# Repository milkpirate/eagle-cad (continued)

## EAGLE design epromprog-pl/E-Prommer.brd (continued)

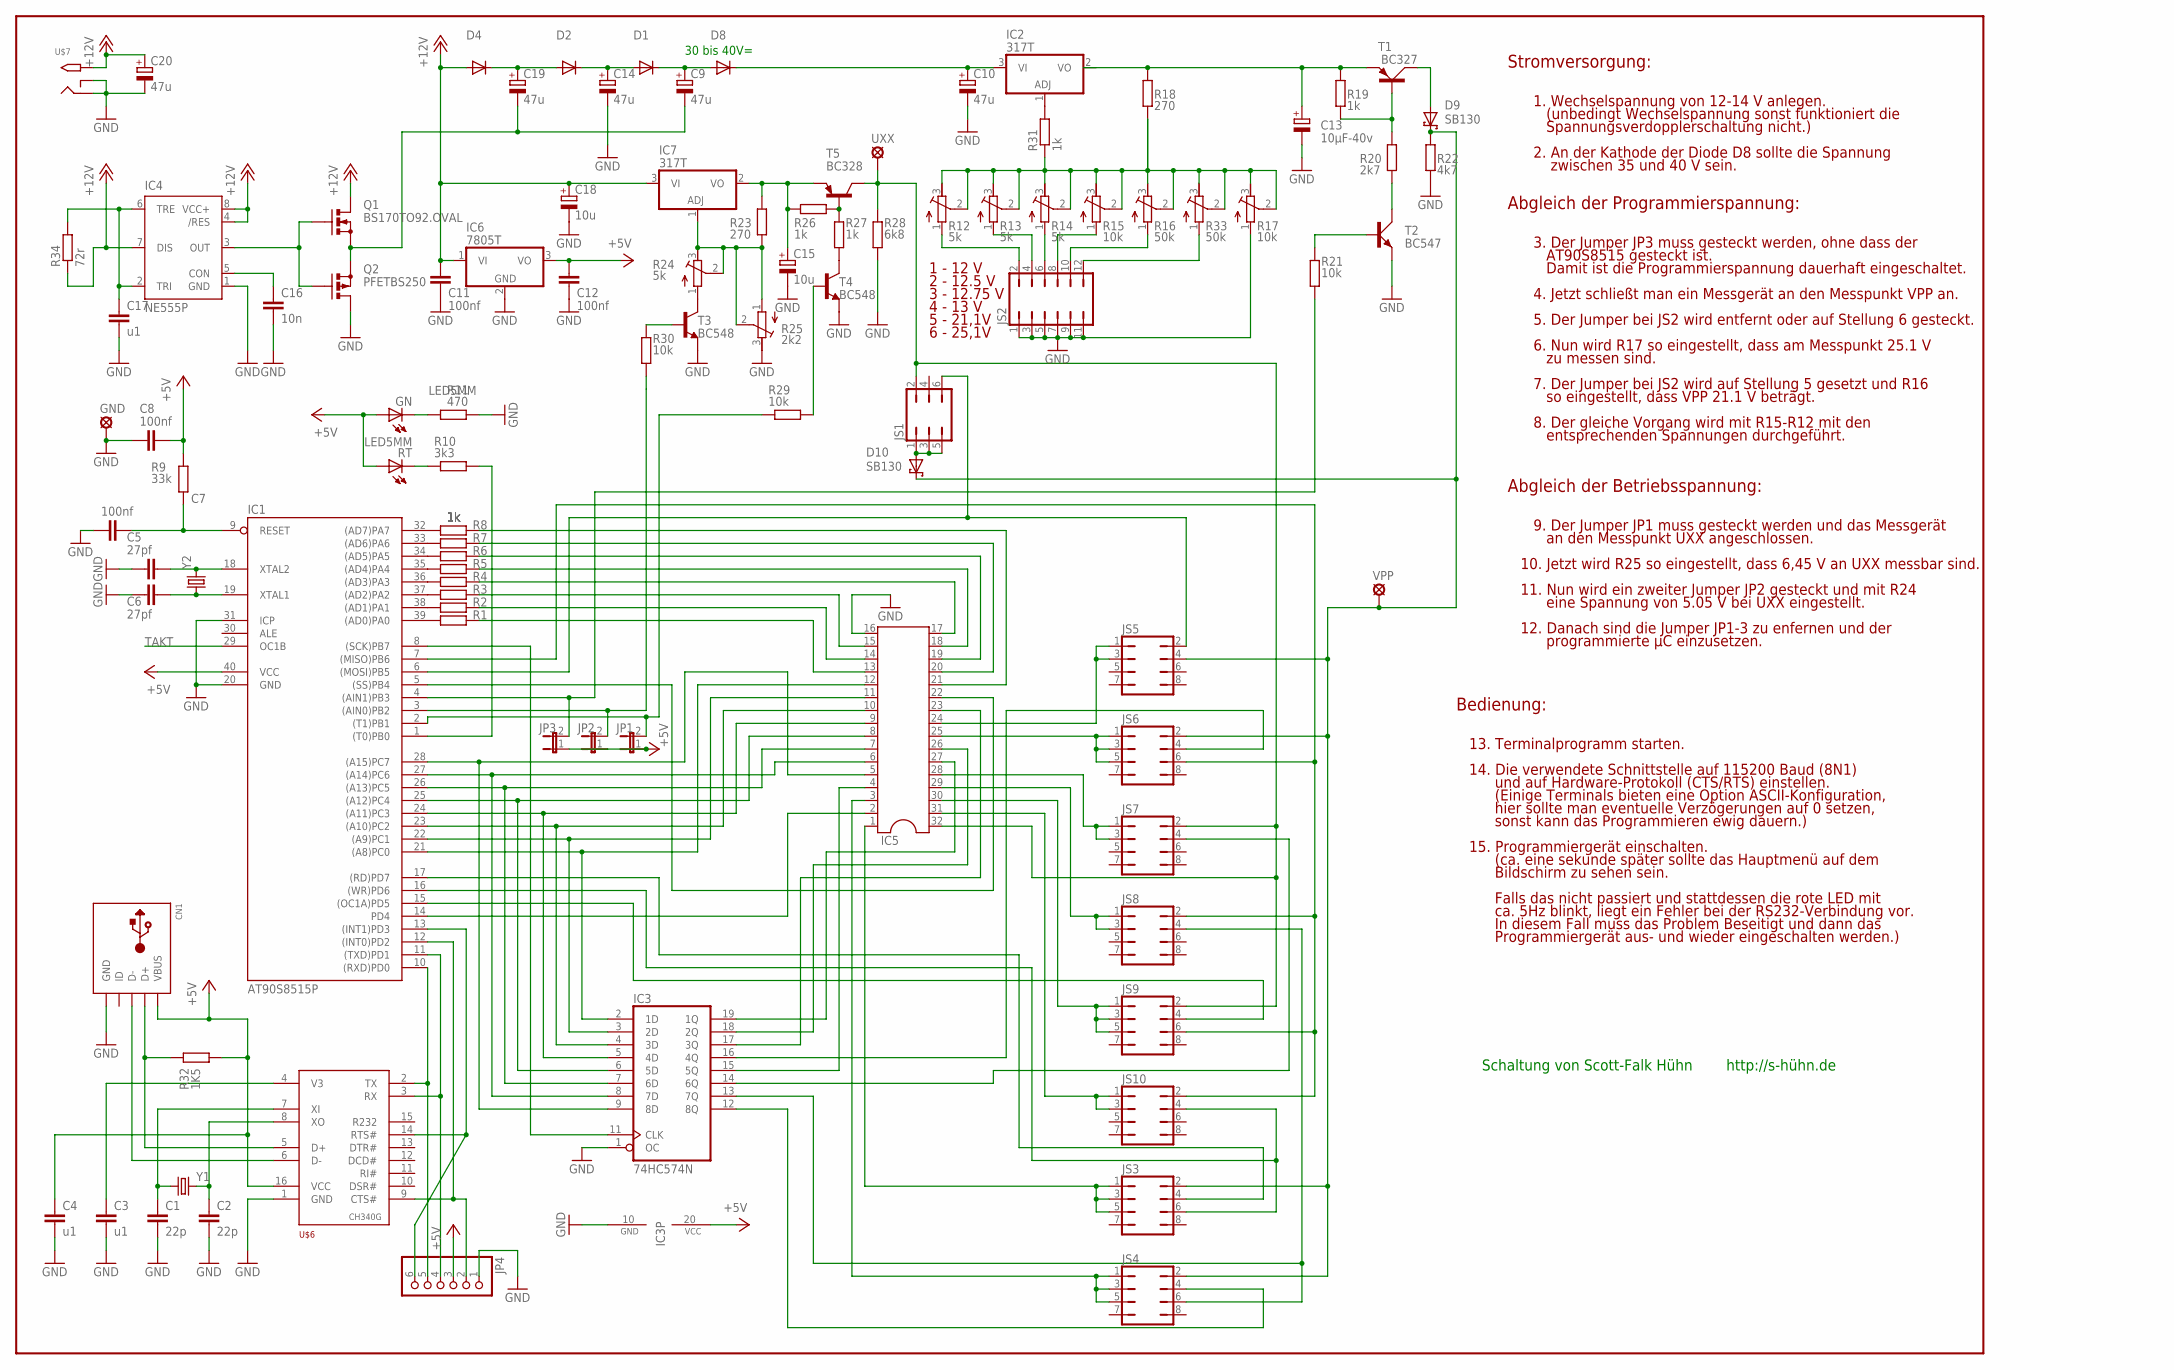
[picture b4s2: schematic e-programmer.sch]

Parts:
C1, C2: 22p; C025-025X050
C3, C4, C17: u1; C025-025X050
C5, C6: 27pf; C025-024X044
C7, C8, C11, C12: 100nf; C025-024X044
C9, C10, C14, C19, C20: 47u; E2,5-7
C13: 10µF-40v; E2,5-5
C15, C18: 10u; E2,5-7
C16: 10n; C025-025X050
CN1: USBTHM; USB-MINIB-THM
D1, D2, D4, D8: 1N4004; DO35-10
D9, D10: SB130; DO35-7
GN: LED5MM
GND: LSP10
IC1: AT90S8515P; DIL40
IC2, IC7: 317T; TO220H
IC3: 74HC574N; DIL20
IC4: NE555P; DIL-08
IC5: DIL32
IC6: 7805T; TO220H
JP1, JP2, JP3: JP1E; JP1
JP4: PINHD-1X6; 1X06
JS1: JP3Q
JS2: JP6Q
JS3, JS4, JS5, JS6, JS7, JS8, JS9, JS10: JP4Q
Q1: BS170TO92.OVAL; TO92-OVAL
Q2: PFETBS250; TO92-OVAL
R1, R2, R3, R4, R5, R6, R7, R8, R19, R26, R27, R31: 1k; 0207/7
R9: 33k; 0204/7
R10: 3k3; 0204/7
R11: 470; 0204/7
R12, R13, R14, R24: 5k; RTRIM3296W
R15, R17: 10k; RTRIM3296W
R16, R33: 50k; RTRIM3296W
R18, R23: 270; 0207/7
R20: 2k7; 0207/7
R21, R29, R30: 10k; 0207/7
R22: 4k7; 0207/7
R25: 2k2; RTRIM3296W
R28: 6k8; 0207/7
R32: 1K5; 0204/7
R34: 72r; 0204/7
RT: LED5MM
T1: BC327; SOT54A
T2: BC547; SOT54A
T3, T4: BC548; TO92
T5: BC328; TO92
U$6: CH340G; SO16
U$7: 2.1MMJACKTHM; PJ-102A
UXX: LSP10
VPP: LSP10
Y1, Y2: CRYSTALHC49US; HC49US

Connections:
!CE: IC1.5 ((SS)PB4), IC5.22
!OE: IC1.6 ((MOSI)PB5), JS1.6, JS5.2
!PR: IC1.7 ((MISO)PB6), JS6.6, JS8.2, JS9.6, JS10.2
+5V: C4.1, C8.2, C12.1, CN1.VBUS, GN.A, IC1.40 (VCC), IC3.20 (VCC), IC6.3 (VO), JP1.1, JP2.1, JP3.1, JP4.3, R9.2, R32.1, RT.A, U$6.16 (VCC)
A0: IC1.21 ((A8)PC0), IC3.2 (1D), IC5.12
A1: IC1.22 ((A9)PC1), IC3.3 (2D), IC5.11
A2: IC1.23 ((A10)PC2), IC3.4 (3D), IC5.10
A3: IC1.24 ((A11)PC3), IC3.5 (4D), IC5.9
A4: IC1.25 ((A12)PC4), IC3.6 (5D), IC5.8
A5: IC1.26 ((A13)PC5), IC3.7 (6D), IC5.7
A6: IC1.27 ((A14)PC6), IC3.8 (7D), IC5.6
A7: IC1.28 ((A15)PC7), IC3.9 (8D), IC5.5
A8: IC3.19 (1Q), IC5.27
A9: IC3.18 (2Q), IC5.26
A10: IC3.17 (3Q), IC5.23
A11: IC3.16 (4Q), JS6.4
A12: IC3.15 (5Q), IC5.4
A13: IC3.14 (6Q), JS7.4
A14: IC3.13 (7Q), JS4.6, JS8.4
A15: IC3.12 (8Q), JS4.4
A16: IC1.14 (PD4), IC5.2
A17: IC1.15 ((OC1A)PD5), JS9.4
A18: IC1.16 ((WR)PD6), JS3.6, JS10.4
A19: IC1.17 ((RD)PD7), JS3.4
CTS: IC1.12 ((INT0)PD2), JP4.2, U$6.9 (CTS#)
D0: IC5.13, R1.2
D1: IC5.14, R2.2
D2: IC5.15, R3.2
D3: IC5.17, R4.2
D4: IC5.18, R5.2
D5: IC5.19, R6.2
D6: IC5.20, R7.2
D7: IC5.21, R8.2
GND: C1.2, C2.2, C3.2, C4.2, C5.1, C6.1, C7.1, C8.1, C10.-, C11.2, C12.2, C13.-, C14.-, C15.-, C16.2, C17.2, C18.-, C20.-, CN1.GND, GND.MP, IC1.20 (GND), IC1.31 (ICP), IC3.1 (OC), IC3.10 (GND), IC4.1 (GND), IC5.16, IC6.2 (GND), JP4.1, JS2.1, JS2.3, JS2.5, JS2.7, JS2.9, JS2.11, Q2.1 (D), R11.2, R17.1 (E), R22.1, R25.3 (A), R28.1, T2.E, T3.1 (E), T4.1 (E), U$6.1 (GND), U$7.RING, U$7.RING_SW; also elsewhere on the board
unnamed: IC1.32 ((AD7)PA7), R8.1
unnamed: IC1.33 ((AD6)PA6), R7.1
unnamed: IC1.34 ((AD5)PA5), R6.1
unnamed: IC1.35 ((AD4)PA4), R5.1
unnamed: IC1.36 ((AD3)PA3), R4.1
unnamed: IC1.37 ((AD2)PA2), R3.1
unnamed: IC1.38 ((AD1)PA1), R2.1
unnamed: IC1.39 ((AD0)PA0), R1.1
unnamed: IC1.8 ((SCK)PB7), IC3.11 (CLK)
unnamed: IC1.10 ((RXD)PD0), JP4.5, U$6.2 (TX)
unnamed: IC1.11 ((TXD)PD1), JP4.4, U$6.3 (RX)
unnamed: CN1.D+, R32.2, U$6.5 (D+)
unnamed: CN1.D-, U$6.6 (D-)
unnamed: C2.1, U$6.8 (XO), Y1.2
unnamed: C1.1, U$6.7 (XI), Y1.1
unnamed: C3.1, U$6.4 (V3)
unnamed: JS2.12, R33.1 (E)
unnamed: R10.1, RT.K (C)
unnamed: C16.1, IC4.5 (CON)
unnamed: C17.1, IC4.2 (TRI), IC4.6 (TRE), R34.2
unnamed: GN.K (C), R11.1
unnamed: IC5.3, JS4.1, JS4.3, JS4.5
unnamed: IC5.1, JS3.1, JS3.3, JS3.5
unnamed: IC5.24, JS5.1, JS5.3
unnamed: C7.2, IC1.9 (RESET), R9.1
unnamed: IC5.25, JS6.1, JS6.3, JS6.5
unnamed: JS2.2, R12.1 (E)
unnamed: JS2.4, R13.1 (E)
unnamed: IC5.28, JS7.1, JS7.3
unnamed: IC5.29, JS8.1, JS8.3
unnamed: IC1.1 ((T0)PB0), R10.2
unnamed: IC5.30, JS9.1, JS9.3, JS9.5
unnamed: JS2.6, R14.1 (E)
unnamed: IC5.31, JS10.1, JS10.3
unnamed: JS2.8, R15.1 (E)
unnamed: JS2.10, R16.1 (E)
unnamed: R12.2 (S), R12.3 (A), R13.2 (S), R13.3 (A), R14.2 (S), R14.3 (A), R15.2 (S), R15.3 (A), R16.2 (S), R16.3 (A), R17.2 (S), R17.3 (A), R18.1, R31.1, R33.2 (S), R33.3 (A)
unnamed: D10.A, JS1.1, JS1.3, JS1.5
unnamed: D9.A, T1.C
unnamed: R26.1, R27.2, T5.2 (B)
unnamed: R27.1, T4.3 (C)
unnamed: IC7.1 (ADJ), R23.1, R24.2 (S), R24.3 (A), R25.1 (E), R25.2 (S)
unnamed: R24.1 (E), T3.3 (C)
unnamed: C15.+, IC7.2 (VO), R23.2, R26.2, T5.1 (E)
unnamed: R29.2, T4.2 (B)
unnamed: C13.+, IC2.2 (VO), R18.2, R19.2, T1.E
unnamed: R30.2, T3.2 (B)
unnamed: R19.1, R20.2, T1.B
unnamed: R20.1, T2.C
unnamed: R21.2, T2.B
unnamed: IC2.1 (ADJ), R31.2
RTS: IC1.13 ((INT1)PD3), JP4.6, U$6.14 (RTS#)
TAKT: IC1.29 (OC1B)
UXX: IC5.32, JS1.2, JS7.2, JS9.2, R28.2, T5.3 (C), UXX.MP
VCC_5/6: IC1.3 ((AIN0)PB2), JP2.2, R30.1
VCC_EIN: IC1.2 ((T1)PB1), JP1.2, R29.1
VPP: D9.C, D10.C, JS3.2, JS4.2, JS5.4, JS6.2, R22.2, VPP.MP
VPP_EIN: IC1.4 ((AIN1)PB3), JP3.2, R21.1

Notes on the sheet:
Schaltung von Scott-Falk Hühn
http://s-hühn.de
1. Wechselspannung von 12-14 V anlegen.
(unbedingt Wechselspannung sonst funktioniert die
Spannungsverdopplerschaltung nicht.)
2. An der Kathode der Diode D8 sollte die Spannung
zwischen 35 und 40 V sein.
3. Der Jumper JP3 muss gesteckt werden, ohne dass der
4. Jetzt schließt man ein Messgerät an den Messpunkt VPP an.
5. Der Jumper bei JS2 wird entfernt oder auf Stellung 6 gesteckt.
6. Nun wird R17 so eingestellt, dass am Messpunkt 25.1 V
zu messen sind.
7. Der Jumper bei JS2 wird auf Stellung 5 gesetzt und R16
so eingestellt, dass VPP 21.1 V beträgt.
8. Der gleiche Vorgang wird mit R15-R12 mit den
entsprechenden Spannungen durchgeführt.
9. Der Jumper JP1 muss gesteckt werden und das Messgerät
an den Messpunkt UXX angeschlossen.
10. Jetzt wird R25 so eingestellt, dass 6,45 V an UXX messbar sind.
11. Nun wird ein zweiter Jumper JP2 gesteckt und mit R24
eine Spannung von 5.05 V bei UXX eingestellt.
Abgleich der Programmierspannung:
Abgleich der Betriebsspannung:
Bedienung:
13. Terminalprogramm starten.
14. Die verwendete Schnittstelle auf 115200 Baud (8N1)
und auf Hardware-Protokoll (CTS/RTS) einstellen.
(Einige Terminals bieten eine Option ASCII-Konfiguration,
hier sollte man eventuelle Verzögerungen auf 0 setzen,
sonst kann das Programmieren ewig dauern.)
15. Programmiergerät einschalten.
(ca. eine sekunde später sollte das Hauptmenü auf dem
Bildschirm zu sehen sein.
Falls das nicht passiert und stattdessen die rote LED mit
ca. 5Hz blinkt, liegt ein Fehler bei der RS232-Verbindung vor.
In diesem Fall muss das Problem Beseitigt und dann das
Programmiergerät aus- und wieder eingeschalten werden.)
Stromversorgung:
1 - 12 V
2 - 12.5 V

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
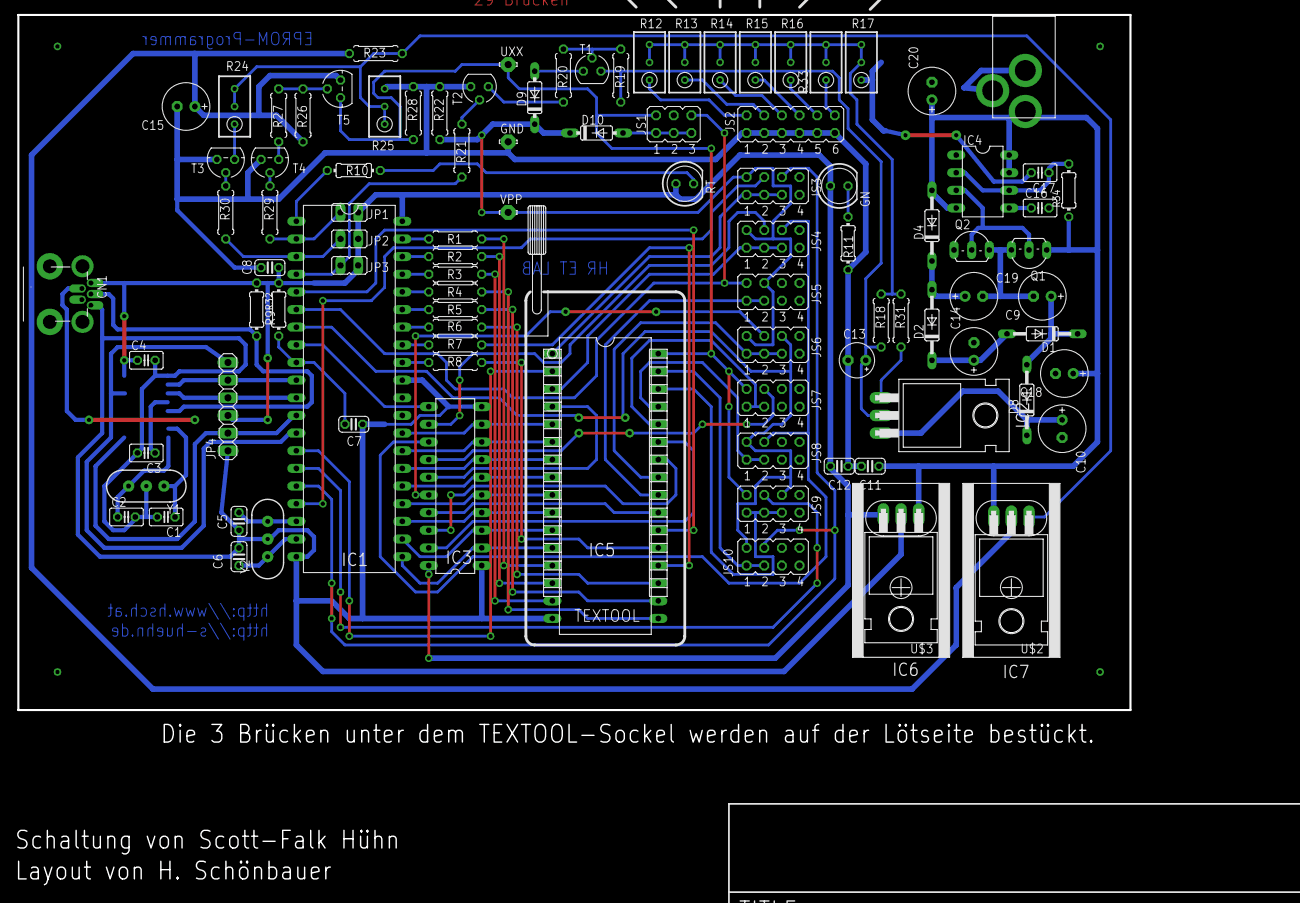
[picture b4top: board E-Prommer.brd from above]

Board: 2 copper layers, 160.0 x 100.0 mm, 103 parts (1 on the bottom side), 100 nets.

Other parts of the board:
U$1: SOCKEL
U$2, U$3: SK12/25
U$4: LETTER_P
U$5: DOCFIELD

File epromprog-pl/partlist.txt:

Partlist

Exported from E-Prommer.sch at 23.09.2014 12:23:19

EAGLE Version 6.1.0 Copyright (c) 1988-2012 CadSoft

Assembly variant: 

Part     Value          Device               Package       Library                 Sheet

C1       22p            C-EU025-025X050      C025-025X050  rcl                     1
C2       22p            C-EU025-025X050      C025-025X050  rcl                     1
C3       u1             C-EU025-025X050      C025-025X050  rcl                     1
C4       u1             C-EU025-025X050      C025-025X050  rcl                     1
C5       27pf           C-EU025-024X044      C025-024X044  rcl                     1
C6       27pf           C-EU025-024X044      C025-024X044  rcl                     1
C7       100nf          C-EU025-024X044      C025-024X044  rcl                     1
C8       100nf          C-EU025-024X044      C025-024X044  rcl                     1
C9       470µF-25v      CPOL-EUE3.5-10       E3,5-10       rcl                     1
C10      470µF-63v      CPOL-EUE5-13         E5-13         rcl                     1
C11      100nf          C-EU025-024X044      C025-024X044  rcl                     1
C12      100nf          C-EU025-024X044      C025-024X044  rcl                     1
C13      10µF-40v       CPOL-EUE2.5-5        E2,5-5        rcl                     1
C14      2200u-30v      CPOL-EUE7.5-18       E7,5-18       rcl                     1
C15      10u            CPOL-EUE2.5-7        E2,5-7        rcl                     1
CN1                     USBTHM               USB-MINIB-THM adafruit                1
D1       1N5060GP       1N5060GP             DO15-12       diode                   1
D2       1N5060GP       1N5060GP             DO15-12       diode                   1
D3       1N4004         DIODE-DO35-10        DO35-10       diode                   1
D8       1N4004         DIODE-DO35-10        DO35-10       diode                   1
D9       SB130          SCHOTTKY-DIODEDO35-7 DO35-7        diode                   1
D10      SB130          SCHOTTKY-DIODEDO35-7 DO35-7        diode                   1
D11      1N5060GP       1N5060GP             DO15-12       diode                   1
D12      1N5060GP       1N5060GP             DO15-12       diode                   1
GN       LED5MM         LED5MM               LED5MM        led                     1
GND      LSP10          LSP10                LSP10         solpad                  1
IC1      AT90S8515P     AT90S8515P           DIL40         atmel                   1
IC2      317T           317T                 TO220H        linear                  1
IC3      74HC574N       74HC574N             DIL20         74xx-us                 1
IC5                     DIL32                DIL32         dil                     1
IC6      7805T          7805T                TO220H        linear                  1
IC7      317T           317T                 TO220H        linear                  1
JP1                     JP1E                 JP1           jumper                  1
JP2                     JP1E                 JP1           jumper                  1
JP3                     JP1E                 JP1           jumper                  1
JP4                     PINHD-1X6            1X06          pinhead                 1
JS1                     JP3Q                 JP3Q          jumper                  1
JS2                     JP6Q                 JP6Q          jumper                  1
JS3                     JP4Q                 JP4Q          jumper                  1
JS4                     JP4Q                 JP4Q          jumper                  1
JS5                     JP4Q                 JP4Q          jumper                  1
JS6                     JP4Q                 JP4Q          jumper                  1
JS7                     JP4Q                 JP4Q          jumper                  1
JS8                     JP4Q                 JP4Q          jumper                  1
JS9                     JP4Q                 JP4Q          jumper                  1
JS10                    JP4Q                 JP4Q          jumper                  1
R1       1k             R-EU_0207/7          0207/7        rcl                     1
R2       1k             R-EU_0207/7          0207/7        rcl                     1
R3       1k             R-EU_0207/7          0207/7        rcl                     1
R4       1k             R-EU_0207/7          0207/7        rcl                     1
R5       1k             R-EU_0207/7          0207/7        rcl                     1
R6       1k             R-EU_0207/7          0207/7        rcl                     1
R7       1k             R-EU_0207/7          0207/7        rcl                     1
R8       1k             R-EU_0207/7          0207/7        rcl                     1
R9       33k            R-EU_0204/7          0204/7        rcl                     1
R10      3k3            R-EU_0204/7          0204/7        rcl                     1
R11      470            R-EU_0204/7          0204/7        rcl                     1
R12      5k             R-TRIMM3296W         RTRIM3296W    rcl                     1
R13      5k             R-TRIMM3296W         RTRIM3296W    rcl                     1
R14      5k             R-TRIMM3296W         RTRIM3296W    rcl                     1
R15      10k            R-TRIMM3296W         RTRIM3296W    rcl                     1
R16      50k            R-TRIMM3296W         RTRIM3296W    rcl                     1
R17      10k            R-TRIMM3296W         RTRIM3296W    rcl                     1
R18      270            R-EU_0207/7          0207/7        rcl                     1
R19      1k             R-EU_0207/7          0207/7        rcl                     1
R20      2k7            R-EU_0207/7          0207/7        rcl                     1
R21      10k            R-EU_0207/7          0207/7        rcl                     1
R22      4k7            R-EU_0207/7          0207/7        rcl                     1
R23      270            R-EU_0207/7          0207/7        rcl                     1
R24      5k             R-TRIMM3296W         RTRIM3296W    rcl                     1
R25      2k2            R-TRIMM3296W         RTRIM3296W    rcl                     1
R26      1k             R-EU_0207/7          0207/7        rcl                     1
R27      1k             R-EU_0207/7          0207/7        rcl                     1
R28      6k8            R-EU_0207/7          0207/7        rcl                     1
R29      10k            R-EU_0207/7          0207/7        rcl                     1
R30      10k            R-EU_0207/7          0207/7        rcl                     1
R31      1k             R-EU_0207/7          0207/7        rcl                     1
R32      1K5            R-EU_0204/7          0204/7        rcl                     1
R33      50k            R-TRIMM3296W         RTRIM3296W    rcl                     1
RT       LED5MM         LED5MM               LED5MM        led                     1
T1       BC327          BC327                SOT54A        transistor-small-signal 1
T2       BC547          BC547                SOT54A        transistor-small-signal 1
T3       BC548          BC547                TO92          transistor-npn          1
T4       BC548          BC547                TO92          transistor-npn          1
T5       BC328          BC327                TO92          transistor-pnp          1
U$6      CH340G         CH340G               SO16          _MY_OWN_LIB             1
U$7      2.1MMJACKTHM   2.1MMJACKTHM         PJ-102A       adafruit                1
UXX      LSP10          LSP10                LSP10         solpad                  1
VPP      LSP10          LSP10                LSP10         solpad                  1
Y1                      CRYSTALHC49US        HC49US        SparkFun-FreqCtrl       1
Y2                      CRYSTALHC49US        HC49US        SparkFun-FreqCtrl       1

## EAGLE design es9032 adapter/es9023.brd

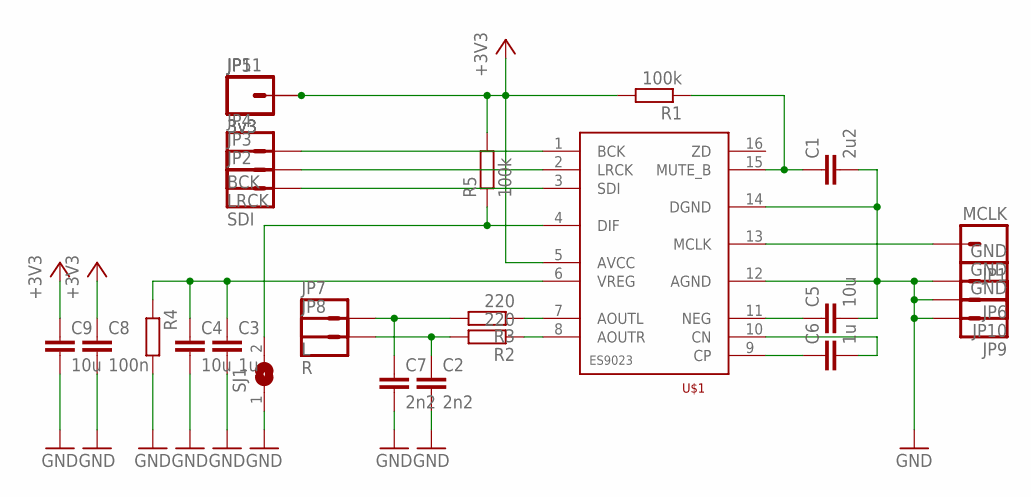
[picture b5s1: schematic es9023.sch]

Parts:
C1: 2u2; C0805K
C2, C7: 2n2; C0805K
C3, C6: 1u; C0805K
C4, C5, C9: 10u; C0805K
C8: 100n; C0805K
JP1: MCLK; 1X01_LONGPAD
JP2: SDI; 1X01_LONGPAD
JP3: LRCK; 1X01_LONGPAD
JP4: BCK; 1X01_LONGPAD
JP5, JP11: 3v3; 1X01_LONGPAD
JP6, JP9, JP10: GND; 1X01_LONGPAD
JP7: L; 1X01_LONGPAD
JP8: R; 1X01_LONGPAD
R1, R5: 100k; M0805
R2, R3: 220; M0805
R4: R-EU_M0805; M0805
SJ1: SJ
U$1: ES9023-SMD; SOP16

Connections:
+3V3: C8.1, C9.1, JP5.1, JP11.1, R1.2, R5.2, U$1.5 (AVCC)
GND: C1.2, C2.2, C3.2, C4.2, C5.2, C7.2, C8.2, C9.2, JP6.1, JP9.1, JP10.1, R4.2, SJ1.1, U$1.12 (AGND), U$1.14 (DGND)
unnamed: C1.1, R1.1, U$1.15 (MUTE_B)
unnamed: C3.1, C4.1, R4.1, U$1.6 (VREG)
unnamed: C5.1, U$1.11 (NEG)
unnamed: C6.2, U$1.10 (CN)
unnamed: C6.1, U$1.9 (CP)
unnamed: R3.1, U$1.7 (AOUTL)
unnamed: R2.1, U$1.8 (AOUTR)
unnamed: JP4.1, U$1.1 (BCK)
unnamed: JP3.1, U$1.2 (LRCK)
unnamed: JP2.1, U$1.3 (SDI)
unnamed: C7.1, JP7.1, R3.2
unnamed: C2.1, JP8.1, R2.2
unnamed: JP1.1, U$1.13 (MCLK)
unnamed: R5.1, SJ1.2, U$1.4 (DIF)

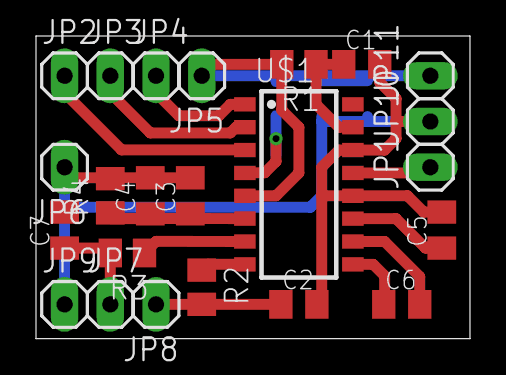
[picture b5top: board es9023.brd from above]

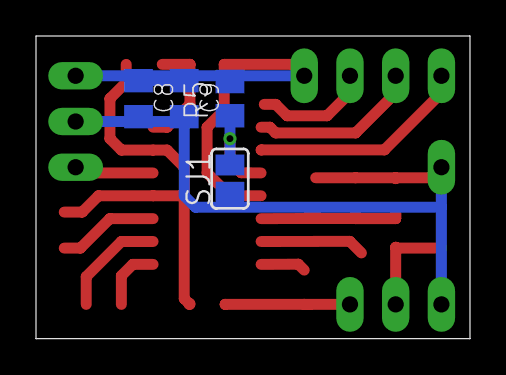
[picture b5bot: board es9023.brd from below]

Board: 2 copper layers, 24.1 x 16.8 mm, 27 parts (4 on the bottom side), 16 nets.
